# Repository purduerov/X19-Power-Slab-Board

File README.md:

# Purdue ROV KiCad Board Template

Starter template for new PCB designs in Purdue ROV. Pre-configured with the team component library submodule, automatic Git clean filters, isolation rules, and CI/CD validation.

---

## 🚀 Quickstart: Opening the Project (Recommended)

**Always open the project using the 1-click launcher:**

* **Windows:** Double-click `LAUNCH_KICAD.bat`
* **macOS / Linux:** Run `./LAUNCH_KICAD.sh`

### What the Launcher Does Automatically:
1. ⚙️ **Configures Git Hooks & Clean Filters:** Sets up Git to strip volatile viewport/zoom coordinates on every commit, preventing merge conflicts.
2. 🔄 **Auto-Updates Component Library:** Pulls the freshest symbols, footprints, and 3D models from `purdue-rov-kicad-lib` before opening.
3. 📐 **Opens KiCad:** Launches the project file with all 6 central library categories pre-linked.

---

## Creating a New Board Repository

1. In GitHub, click **Use this template** > **Create a new repository**.
2. Name the repo to match the board function (e.g. `thruster-interface-board`).
3. Clone recursively so submodules are pulled:
   ```bash
   git clone --recursive https://github.com/purduerov/<your-repo-name>.git
   cd <your-repo-name>
   ```
   If cloned without `--recursive`, initialize the submodule:
   ```bash
   git submodule update --init --recursive
   ```

4. Prepare the board with `bootstrap.py` (renames starter files, writes the manifest, and installs the validation hook; `LAUNCH_KICAD` runs this automatically):
   ```bash
   python bootstrap.py --project-dir . --non-interactive
   ```

## Central Component Library & Manager GUI

The template is pre-configured with project-level library tables (`sym-lib-table` and `fp-lib-table`) pointing to `purdue-rov-kicad-lib`:
- `rov_passives`: Resistors, capacitors, inductors, crystals
- `rov_power`: Voltage regulators, buck/boost converters, MOSFETs, diodes
- `rov_logic`: MCUs, logic ICs, op-amps, level shifters, transceivers
- `rov_connectors`: Power terminals, XT60/XT30, headers, USB, JST connectors
- `rov_sensors`: IMUs, temperature, pressure sensors
- `rov_mech`: Mounting holes, standoffs, test points

### Launching the Library Manager GUI
To browse parts, inspect footprints, edit properties, or add/delete components in the shared library:
- **Windows:** Double-click `libs\purdue-rov-kicad-lib\LIBRARY_MANAGER.bat`
- **macOS / Linux:** Run `./libs/purdue-rov-kicad-lib/LIBRARY_MANAGER.sh`

## Design Rules & Clearances

- Clearance rules are defined in `custom_rules.kicad_dru`.
- High-power thruster nets require a minimum 2.0 mm clearance from low-voltage logic (3.3V / 5V).

## Automated CI/CD & DevOps Preflight Checks

All CI/CD automation and tooling are centralized in [`purduerov/pcb-devops`](https://github.com/purduerov/pcb-devops):
1. **Automated Git Clean Filters:** Configured automatically by `.githooks/pre-commit` to prevent viewport/zoom merge noise.
2. **KiCad Symbol Linting:** Validates mandatory fields (`MPN`, `Manufacturer`, `Category`, `DigiKey`, `Datasheet`, `Temp_Range`) on all library components.
3. **ERC & DRC Validation:** Executes Electrical and Design Rules Checks via KiBot in GitHub Actions.
4. **Artifact Generation:** Automatically exports Schematic PDFs, Board Layout PDFs, and Interactive HTML BOMs on every pull request.

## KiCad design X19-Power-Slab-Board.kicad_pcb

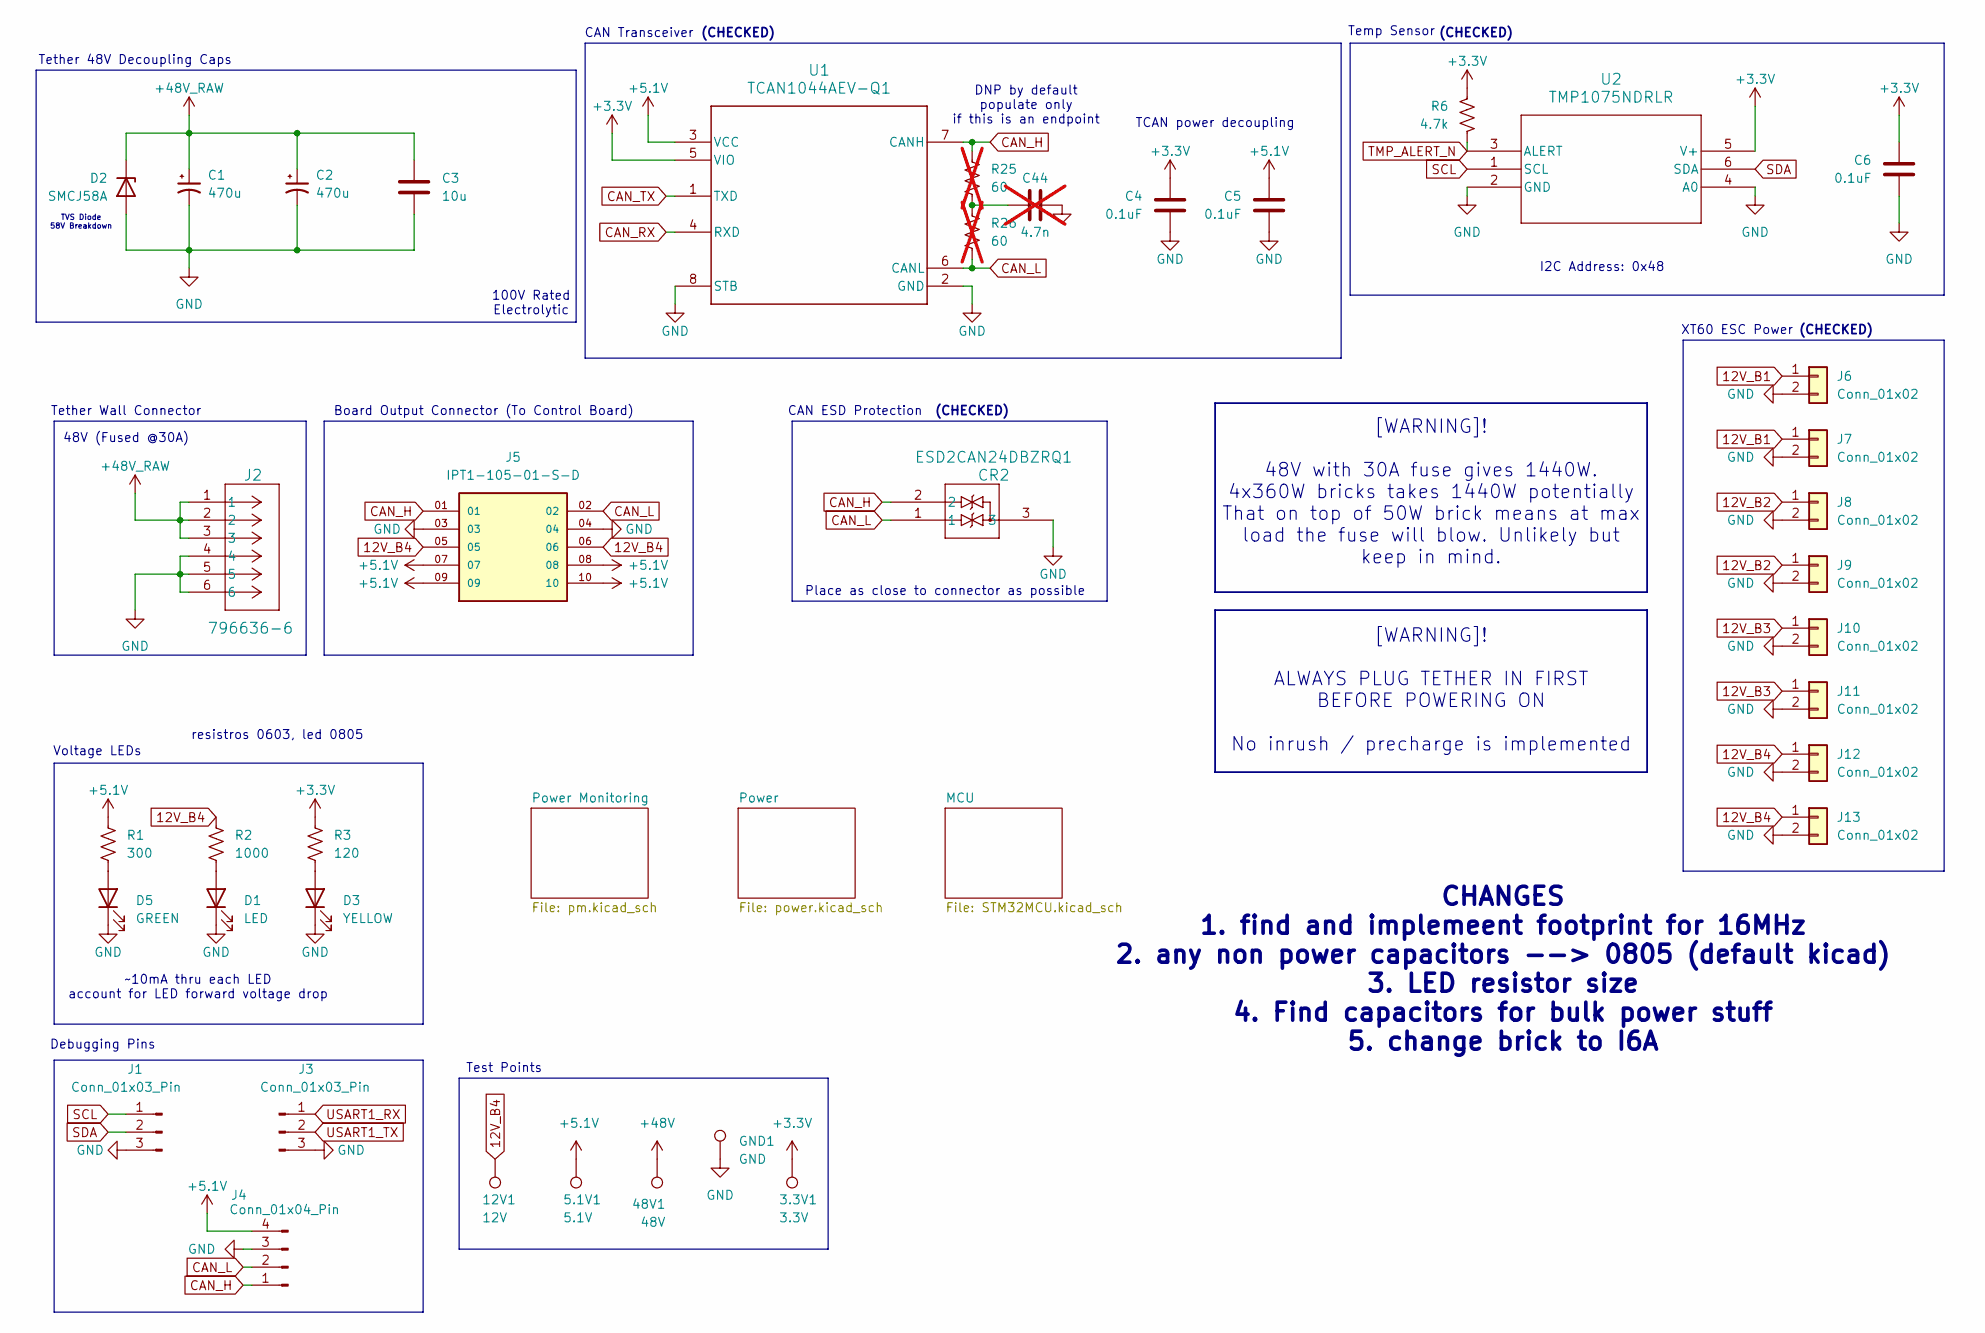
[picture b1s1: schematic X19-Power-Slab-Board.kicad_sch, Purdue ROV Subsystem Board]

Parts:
3.3V1: 3.3V; TestPoint_Pad_D2.5mm
5.1V1: 5.1V; TestPoint_Pad_D2.5mm
12V1: 12V; TestPoint_Pad_D4.0mm
48V1: 48V; TestPoint_Pad_D4.0mm
C1, C2: 470u; CP_Radial_D13.0mm_P5.00mm
C3: 10u; C_1206_3216Metric_Pad1.33x1.80mm_HandSolder
C4, C5, C6: 0.1uF; C_0603_1608Metric_Pad1.08x0.95mm_HandSolder
C44: 4.7n; C_0603_1608Metric_Pad1.08x0.95mm_HandSolder; not fitted
CR2: ESD2CAN24DBZRQ1; SOT-23_Handsoldering
D1: LED; LED_0805_2012Metric_Pad1.15x1.40mm_HandSolder
D2: SMCJ58A; D_SMC
D3: YELLOW; LED_0805_2012Metric_Pad1.15x1.40mm_HandSolder
D5: GREEN; LED_0805_2012Metric_Pad1.15x1.40mm_HandSolder
GND1: GND; TestPoint_Pad_D2.5mm
J1, J3: Conn_01x03_Pin; PinHeader_1x03_P2.54mm_Vertical
J2: 796636-6; CON6_P5MM_VER_TERM-BLK_TYC
J4: Conn_01x04_Pin; PinHeader_1x04_P2.54mm_Vertical
J5: IPT1-105-01-S-D; SAMTEC_IPT1-105-01-S-D; PARTREV R
J6, J7, J8, J9, J10, J11, J12, J13: Conn_01x02; AMASS_XT60PB-M
R1: 300; R_0603_1608Metric_Pad0.98x0.95mm_HandSolder
R2: 1000; R_0603_1608Metric_Pad0.98x0.95mm_HandSolder
R3: 120; R_0603_1608Metric_Pad0.98x0.95mm_HandSolder
R6: 4.7k; R_0603_1608Metric_Pad0.98x0.95mm_HandSolder
R25, R26: 60; R_0603_1608Metric_Pad0.98x0.95mm_HandSolder; not fitted
U1: TCAN1044AEV-Q1; D0008A-IPC_A
U2: TMP1075NDRLR; SOT5X3-6_DRL_TEX

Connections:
12V_B1: J6.1, J7.1; also elsewhere on the board
12V_B2: J8.1, J9.1; also elsewhere on the board
12V_B3: J10.1, J11.1; also elsewhere on the board
12V_B4: 12V1.1 (1_1), J5.05, J5.06, J12.1, J13.1, R2.2; also elsewhere on the board
+3.3V: 3.3V1.1 (1_1), C4.1, C6.1, R3.2, R6.1, U1.5 (VIO), U2.5 (V+); also elsewhere on the board
+5.1V: 5.1V1.1 (1_1), C5.1, J4.4, J5.07, J5.08, J5.09, J5.10, R1.2, U1.3 (VCC); also elsewhere on the board
+48V: 48V1.1 (1_1); also elsewhere on the board
+48V_RAW: C1.1, C2.1, C3.1, D2.1 (K), J2.1, J2.2, J2.3; also elsewhere on the board
CAN_H: CR2.2, J4.1, J5.01, R25.1, U1.7 (CANH)
CAN_L: CR2.1, J4.2, J5.02, R26.2, U1.6 (CANL)
CAN_RX: U1.4 (RXD); also elsewhere on the board
CAN_TX: U1.1 (TXD); also elsewhere on the board
GND: C1.2, C2.2, C3.2, C4.2, C5.2, C6.2, C44.2, CR2.3, D1.1 (K), D2.2 (A), D3.1 (K), D5.1 (K), GND1.1 (1_1), J1.3, J2.4, J2.5, J2.6, J3.3, J4.3, J5.03, J5.04, J6.2, J7.2, J8.2, J9.2, J10.2, J11.2, J12.2, J13.2, U1.2 (GND), U1.8 (STB), U2.2 (GND), U2.4 (A0); also elsewhere on the board
unnamed: C44.1, R25.2, R26.1
unnamed: D1.2 (A), R2.1
unnamed: D3.2 (A), R3.1
unnamed: D5.2 (A), R1.1
SCL: J1.1, U2.1 (SCL); also elsewhere on the board
SDA: J1.2, U2.6 (SDA); also elsewhere on the board
TMP_ALERT_N: R6.2, U2.3 (ALERT); also elsewhere on the board
USART1_RX: J3.1; also elsewhere on the board
USART1_TX: J3.2; also elsewhere on the board

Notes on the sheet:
TCAN power decoupling
(CHECKED)
resistros 0603, led 0805
100V Rated Electrolytic
XT60 ESC Power
CAN Transceiver
I2C Address: 0x48
DNP by default populate only if this is an endpoint
[WARNING]! 48V with 30A fuse gives 1440W. 4x360W bricks takes 1440W potentially That on top of 50W brick means at max load the fuse will blow. Unlikely but keep in mind.
Place as close to connector as possible
Temp Sensor
Board Output Connector (To Control Board)
TVS Diode 58V Breakdown
~10mA thru each LED account for LED forward voltage drop
CAN ESD Protection
Tether 48V Decoupling Caps
Voltage LEDs
CHANGES 1. find and implemeent footprint for 16MHz 2. any non power capacitors --> 0805 (default kicad) 3. LED resistor size 4. Find capacitors for bulk power stuff 5. change brick to I6A
[WARNING]! ALWAYS PLUG TETHER IN FIRST BEFORE POWERING ON No inrush / precharge is implemented
Test Points
Debugging Pins
Tether Wall Connector
48V (Fused @30A)

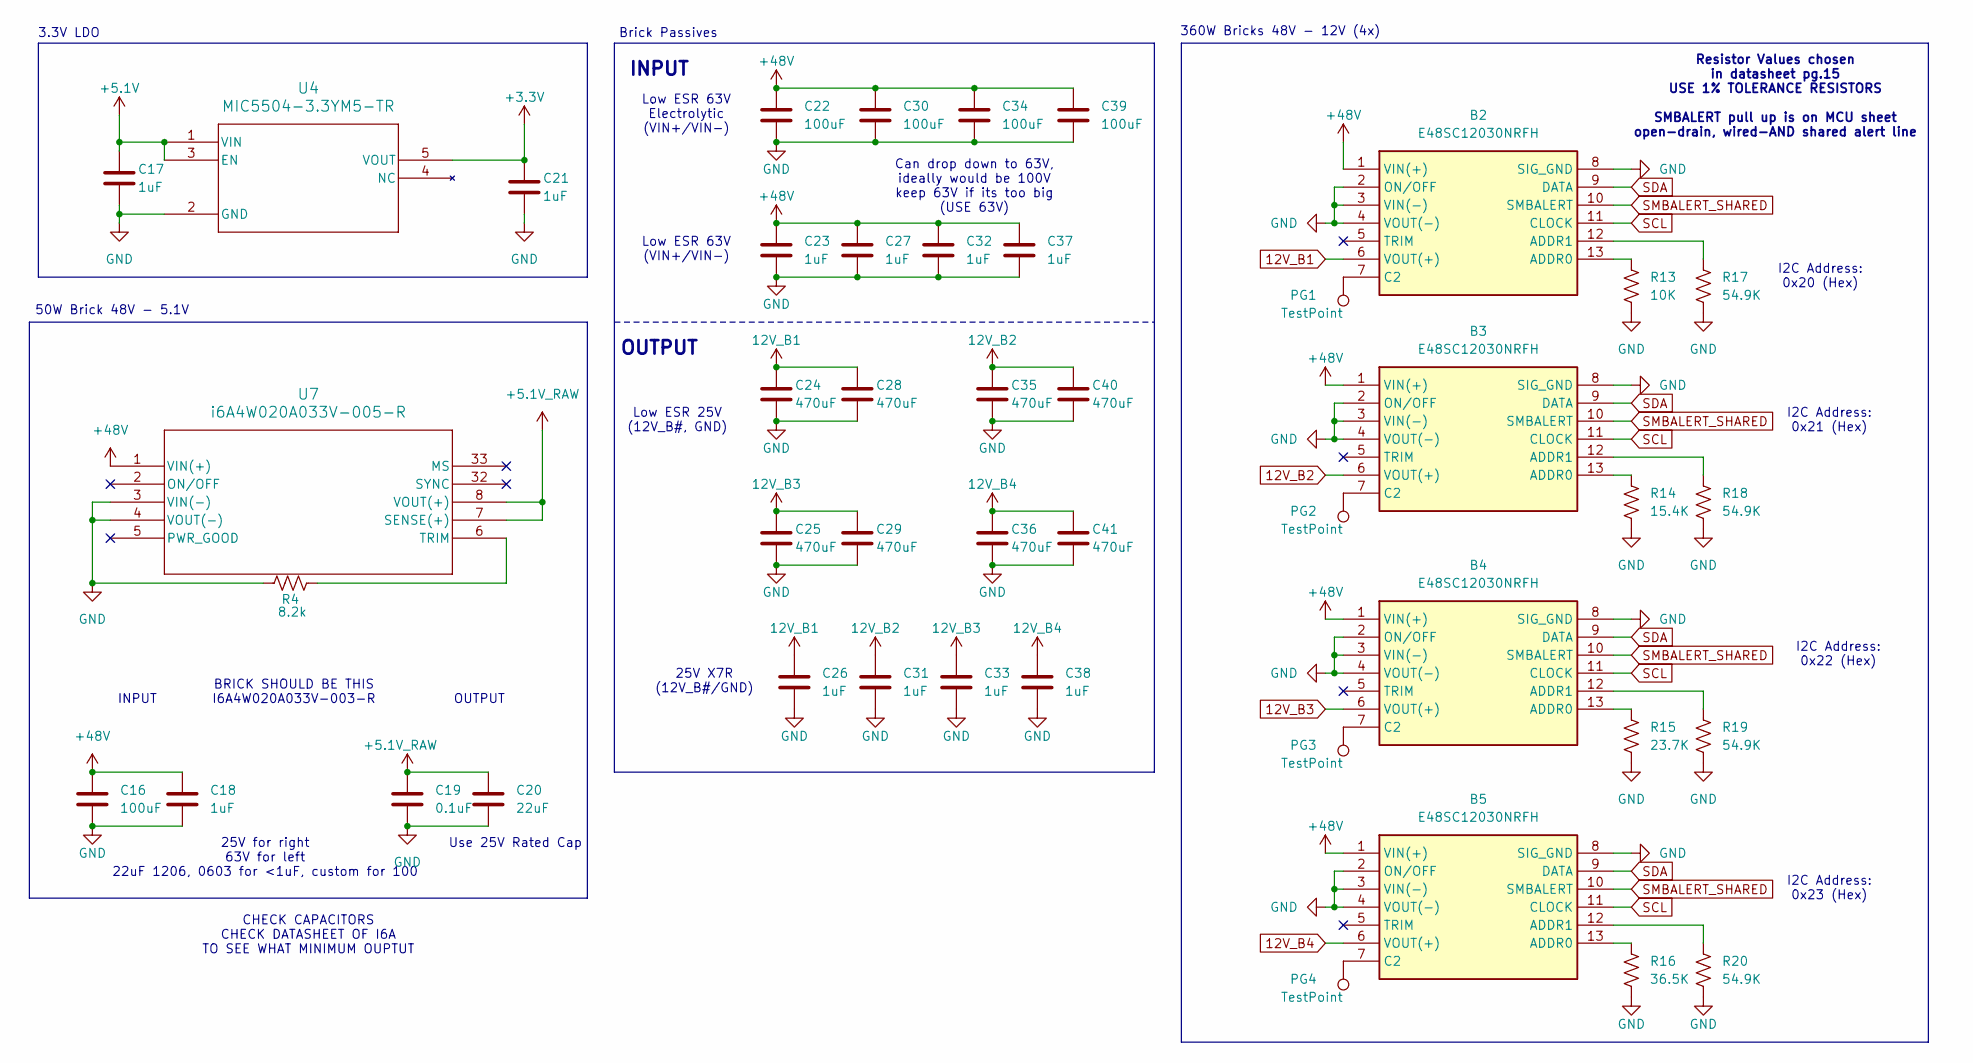
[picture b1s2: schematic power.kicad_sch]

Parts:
B2, B3, B4, B5: E48SC12030NRFH; Manufacturer_Part_Number E48SC12030NRFH
C16, C22, C30, C34, C39: 100uF; CP_Radial_D10.0mm_P5.00mm
C17, C18, C21: 1uF; C_0603_1608Metric_Pad1.08x0.95mm_HandSolder
C19: 0.1uF; C_0603_1608Metric_Pad1.08x0.95mm_HandSolder
C20: 22uF; C_1206_3216Metric_Pad1.33x1.80mm_HandSolder
C23, C26, C27, C31, C32, C33, C37, C38: 1uF; C_0805_2012Metric_Pad1.18x1.45mm_HandSolder
C24, C25, C28, C29, C35, C36, C40, C41: 470uF; CP_Radial_D10.0mm_P5.00mm
PG1, PG2, PG3, PG4: TestPoint; TestPoint_Pad_D2.5mm
R4: 8.2k; R_0603_1608Metric_Pad0.98x0.95mm_HandSolder
R13: 10K; R_0603_1608Metric_Pad0.98x0.95mm_HandSolder
R14: 15.4K; R_0603_1608Metric_Pad0.98x0.95mm_HandSolder
R15: 23.7K; R_0603_1608Metric_Pad0.98x0.95mm_HandSolder
R16: 36.5K; R_0603_1608Metric_Pad0.98x0.95mm_HandSolder
R17, R18, R19, R20: 54.9K; R_0603_1608Metric_Pad0.98x0.95mm_HandSolder
U4: MIC5504-3.3YM5-TR; SOT-23-5_MC_MCH
U7: i6A4W020A033V-005-R; i6A4W_DIP_FULL_TDK

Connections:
12V_B1: B2.6 (VOUT(+)), C24.1, C26.1, C28.1; also elsewhere on the board
12V_B2: B3.6 (VOUT(+)), C31.1, C35.1, C40.1; also elsewhere on the board
12V_B3: B4.6 (VOUT(+)), C25.1, C29.1, C33.1; also elsewhere on the board
12V_B4: B5.6 (VOUT(+)), C36.1, C38.1, C41.1; also elsewhere on the board
+3.3V: C21.1, U4.5 (VOUT); also elsewhere on the board
+5.1V: C17.1, U4.1 (VIN), U4.3 (EN); also elsewhere on the board
+5.1V_RAW: C19.1, C20.1, U7.7 (SENSE(+)), U7.8 (VOUT(+)); also elsewhere on the board
+48V: B2.1 (VIN(+)), B3.1 (VIN(+)), B4.1 (VIN(+)), B5.1 (VIN(+)), C16.1, C18.1, C22.1, C23.1, C27.1, C30.1, C32.1, C34.1, C37.1, C39.1, U7.1 (VIN(+)); also elsewhere on the board
GND: B2.2 (ON/OFF), B2.3 (VIN(-)), B2.4 (VOUT(-)), B2.8 (SIG_GND), B3.2 (ON/OFF), B3.3 (VIN(-)), B3.4 (VOUT(-)), B3.8 (SIG_GND), B4.2 (ON/OFF), B4.3 (VIN(-)), B4.4 (VOUT(-)), B4.8 (SIG_GND), B5.2 (ON/OFF), B5.3 (VIN(-)), B5.4 (VOUT(-)), B5.8 (SIG_GND), C16.2, C17.2, C18.2, C19.2, C20.2, C21.2, C22.2, C23.2, C24.2, C25.2, C26.2, C27.2, C28.2, C29.2, C30.2, C31.2, C32.2, C33.2, C34.2, C35.2, C36.2, C37.2, C38.2, C39.2, C40.2, C41.2, R4.1, R13.2, R14.2, R15.2, R16.2, R17.2, R18.2, R19.2, R20.2, U4.2 (GND), U7.3 (VIN(-)), U7.4 (VOUT(-)); also elsewhere on the board
unnamed: B2.13 (ADDR0), R13.1
unnamed: B2.12 (ADDR1), R17.1
unnamed: B2.7 (C2), PG1.1 (1_1)
unnamed: B3.13 (ADDR0), R14.1
unnamed: B3.12 (ADDR1), R18.1
unnamed: B3.7 (C2), PG2.1 (1_1)
unnamed: B4.13 (ADDR0), R15.1
unnamed: B4.12 (ADDR1), R19.1
unnamed: B4.7 (C2), PG3.1 (1_1)
unnamed: B5.13 (ADDR0), R16.1
unnamed: B5.12 (ADDR1), R20.1
unnamed: B5.7 (C2), PG4.1 (1_1)
unnamed: R4.2, U7.6 (TRIM)
SCL: B2.11 (CLOCK), B3.11 (CLOCK), B4.11 (CLOCK), B5.11 (CLOCK); also elsewhere on the board
SDA: B2.9 (DATA), B3.9 (DATA), B4.9 (DATA), B5.9 (DATA); also elsewhere on the board
SMBALERT_SHARED: B2.10 (SMBALERT), B3.10 (SMBALERT), B4.10 (SMBALERT), B5.10 (SMBALERT); also elsewhere on the board

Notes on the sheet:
3.3V LDO
CHECK CAPACITORS CHECK DATASHEET OF I6A TO SEE WHAT MINIMUM OUPTUT
360W Bricks 48V - 12V (4x)
Brick Passives
Low ESR 63V (VIN+/VIN-)
50W Brick 48V - 5.1V
Use 25V Rated Cap
OUTPUT
INPUT
I2C Address: 0x21 (Hex)
Low ESR 63V Electrolytic (VIN+/VIN-)
I2C Address: 0x20 (Hex)
Low ESR 25V (12V_B#, GND)
25V for right 63V for left 22uF 1206, 0603 for <1uF, custom for 100
BRICK SHOULD BE THIS I6A4W020A033V-003-R
Resistor Values chosen in datasheet pg.15 USE 1% TOLERANCE RESISTORS SMBALERT pull up is on MCU sheet open-drain, wired-AND shared alert line
25V X7R (12V_B#/GND)
I2C Address: 0x22 (Hex)
Can drop down to 63V, ideally would be 100V keep 63V if its too big (USE 63V)
I2C Address: 0x23 (Hex)

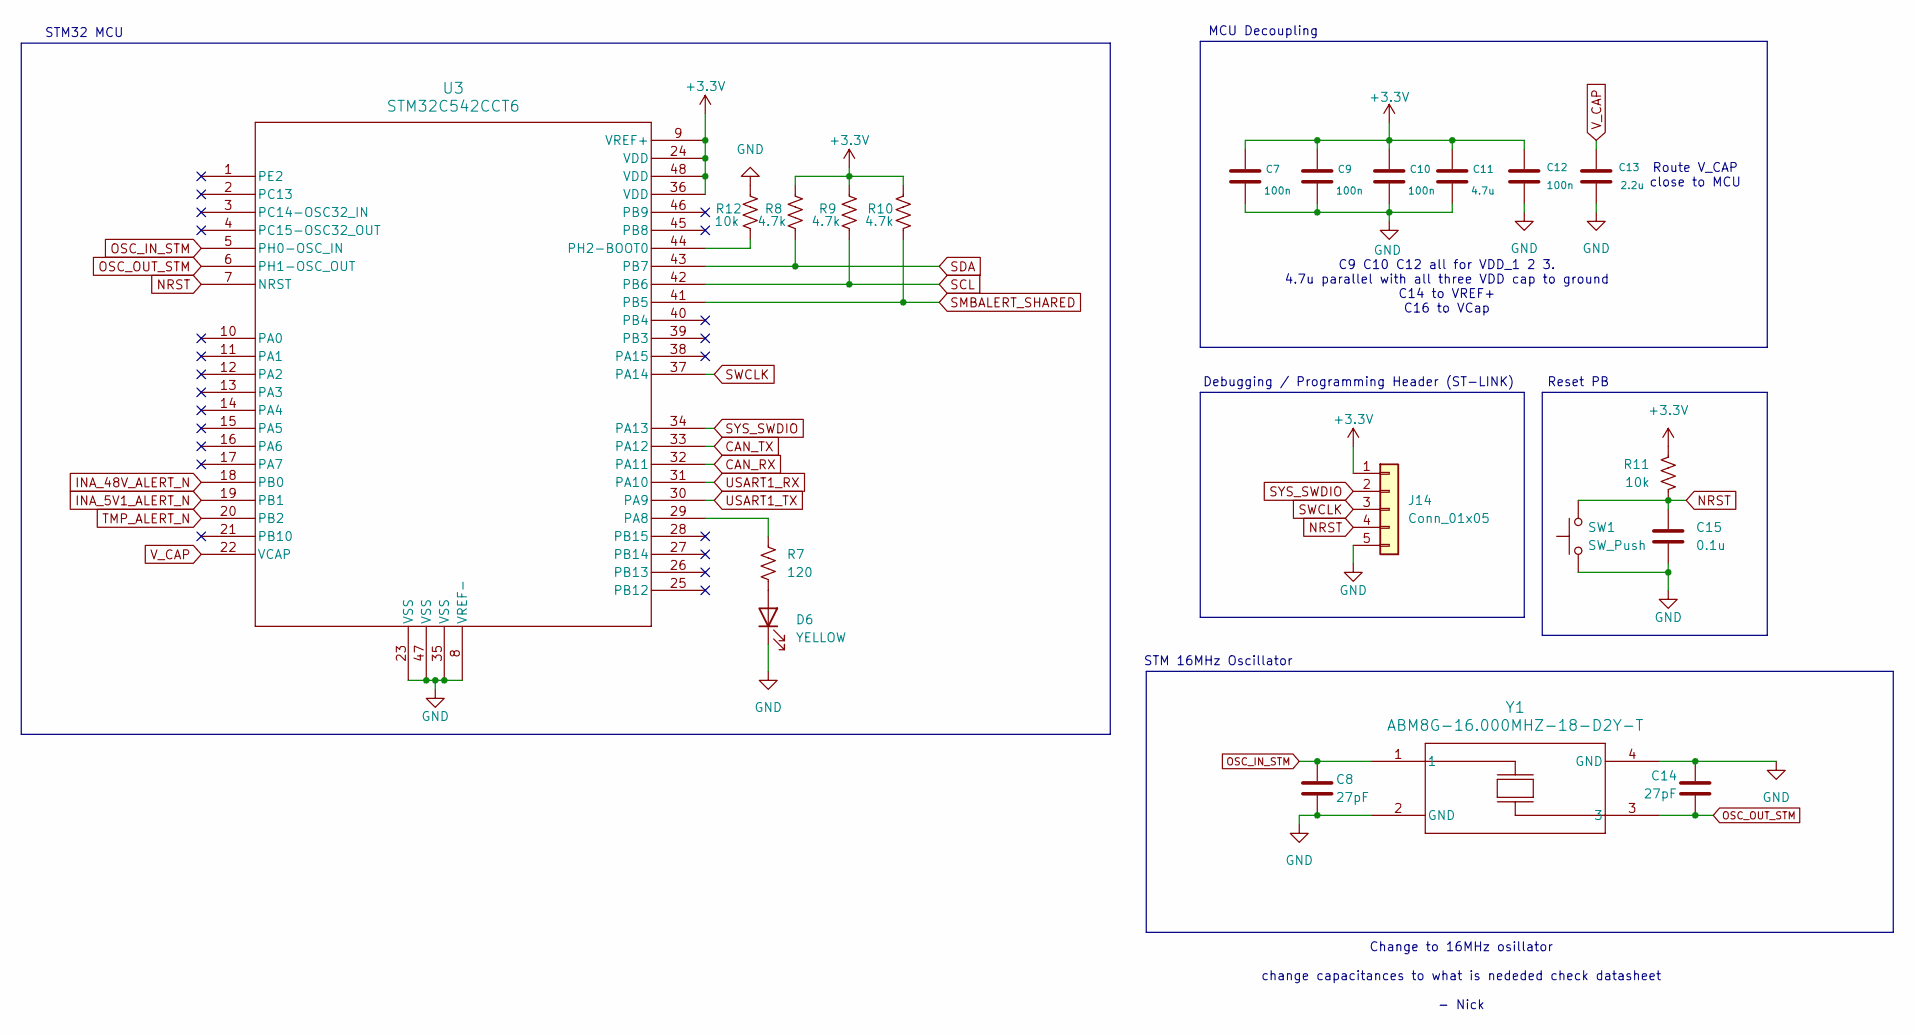
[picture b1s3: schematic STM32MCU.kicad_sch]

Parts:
C7, C9, C10, C12: 100n; C_0603_1608Metric_Pad1.08x0.95mm_HandSolder
C8, C14: 27pF; C_0603_1608Metric_Pad1.08x0.95mm_HandSolder
C11: 4.7u; C_0603_1608Metric_Pad1.08x0.95mm_HandSolder
C13: 2.2u; C_0603_1608Metric_Pad1.08x0.95mm_HandSolder
C15: 0.1u; C_0603_1608Metric_Pad1.08x0.95mm_HandSolder
D6: YELLOW; LED_0805_2012Metric_Pad1.15x1.40mm_HandSolder
J14: Conn_01x05; PinHeader_1x05_P2.54mm_Vertical
R7: 120; R_0603_1608Metric_Pad0.98x0.95mm_HandSolder
R8, R9, R10: 4.7k; R_0603_1608Metric_Pad0.98x0.95mm_HandSolder
R11, R12: 10k; R_0603_1608Metric_Pad0.98x0.95mm_HandSolder
SW1: SW_Push; SW_SPST_B3U-1000P
U3: STM32C542CCT6; LQFP48-7X7
Y1: ABM8G-16.000MHZ-18-D2Y-T; Crystal_SMD_3225-4Pin_3.2x2.5mm

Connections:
+3.3V: C7.1, C9.1, C10.1, C11.1, C12.1, J14.1, R8.2, R9.2, R10.1, R11.1, U3.9 (VREF+), U3.24 (VDD), U3.36 (VDD), U3.48 (VDD); also elsewhere on the board
CAN_RX: U3.32 (PA11); also elsewhere on the board
CAN_TX: U3.33 (PA12); also elsewhere on the board
GND: C7.2, C8.1, C9.2, C10.2, C11.2, C12.2, C13.2, C14.1, C15.2, D6.1 (K), J14.5, R12.2, SW1.1, U3.8 (VREF-), U3.23 (VSS), U3.35 (VSS), U3.47 (VSS), Y1.2 (GND), Y1.4 (GND); also elsewhere on the board
INA_5V1_ALERT_N: U3.19 (PB1); also elsewhere on the board
INA_48V_ALERT_N: U3.18 (PB0); also elsewhere on the board
NRST: C15.1, J14.4, R11.2, SW1.2, U3.7 (NRST)
unnamed: D6.2 (A), R7.2
unnamed: R7.1, U3.29 (PA8)
unnamed: R12.1, U3.44 (PH2-BOOT0)
OSC_IN_STM: C8.2, U3.5 (PH0-OSC_IN), Y1.1
OSC_OUT_STM: C14.2, U3.6 (PH1-OSC_OUT), Y1.3
SCL: R9.1, U3.42 (PB6); also elsewhere on the board
SDA: R8.1, U3.43 (PB7); also elsewhere on the board
SMBALERT_SHARED: R10.2, U3.41 (PB5); also elsewhere on the board
SWCLK: J14.3, U3.37 (PA14)
SYS_SWDIO: J14.2, U3.34 (PA13)
TMP_ALERT_N: U3.20 (PB2); also elsewhere on the board
USART1_RX: U3.31 (PA10); also elsewhere on the board
USART1_TX: U3.30 (PA9); also elsewhere on the board
V_CAP: C13.1, U3.22 (VCAP)

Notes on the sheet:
C9 C10 C12 all for VDD_1 2 3. 4.7u parallel with all three VDD cap to ground C14 to VREF+ C16 to VCap
Reset PB
Change to 16MHz osillator change capacitances to what is nededed check datasheet - Nick
Debugging / Programming Header (ST-LINK)
STM32 MCU
STM 16MHz Oscillator
MCU Decoupling
Route V_CAP close to MCU

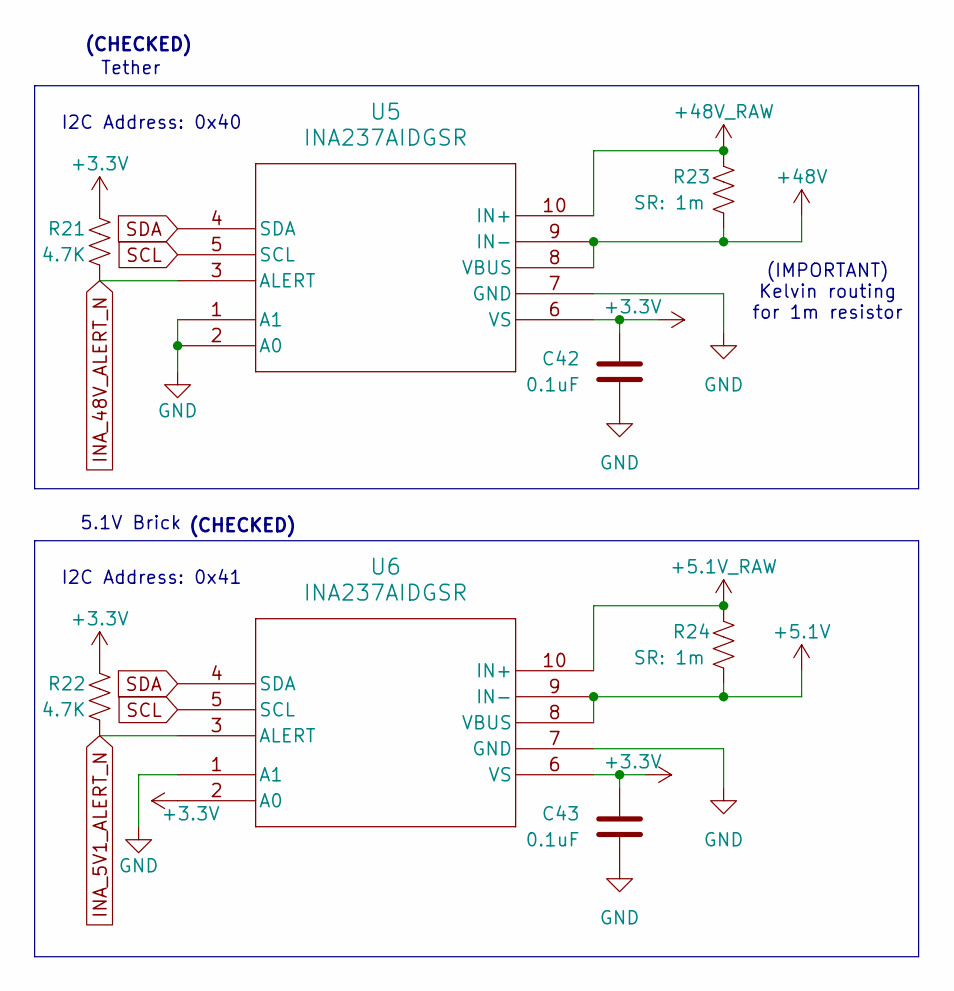
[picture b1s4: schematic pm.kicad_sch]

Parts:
C42, C43: 0.1uF; C_0603_1608Metric_Pad1.08x0.95mm_HandSolder
R21, R22: 4.7K; R_0603_1608Metric_Pad0.98x0.95mm_HandSolder
R23, R24: SR: 1m; R_2512_6332Metric_Pad1.40x3.35mm_HandSolder
U5, U6: INA237AIDGSR; VSSOP_IDGSR_TEX

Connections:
+3.3V: C42.1, C43.1, R21.1, R22.1, U5.6 (VS), U6.2 (A0), U6.6 (VS); also elsewhere on the board
+5.1V: R24.2, U6.8 (VBUS), U6.9 (IN-); also elsewhere on the board
+5.1V_RAW: R24.1, U6.10 (IN+); also elsewhere on the board
+48V: R23.2, U5.8 (VBUS), U5.9 (IN-); also elsewhere on the board
+48V_RAW: R23.1, U5.10 (IN+); also elsewhere on the board
GND: C42.2, C43.2, U5.1 (A1), U5.2 (A0), U5.7 (GND), U6.1 (A1), U6.7 (GND); also elsewhere on the board
INA_5V1_ALERT_N: R22.2, U6.3 (ALERT); also elsewhere on the board
INA_48V_ALERT_N: R21.2, U5.3 (ALERT); also elsewhere on the board
SCL: U5.5 (SCL), U6.5 (SCL); also elsewhere on the board
SDA: U5.4 (SDA), U6.4 (SDA); also elsewhere on the board

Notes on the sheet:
Tether
(IMPORTANT) Kelvin routing for 1m resistor
(CHECKED)
5.1V Brick
I2C Address: 0x41
I2C Address: 0x40

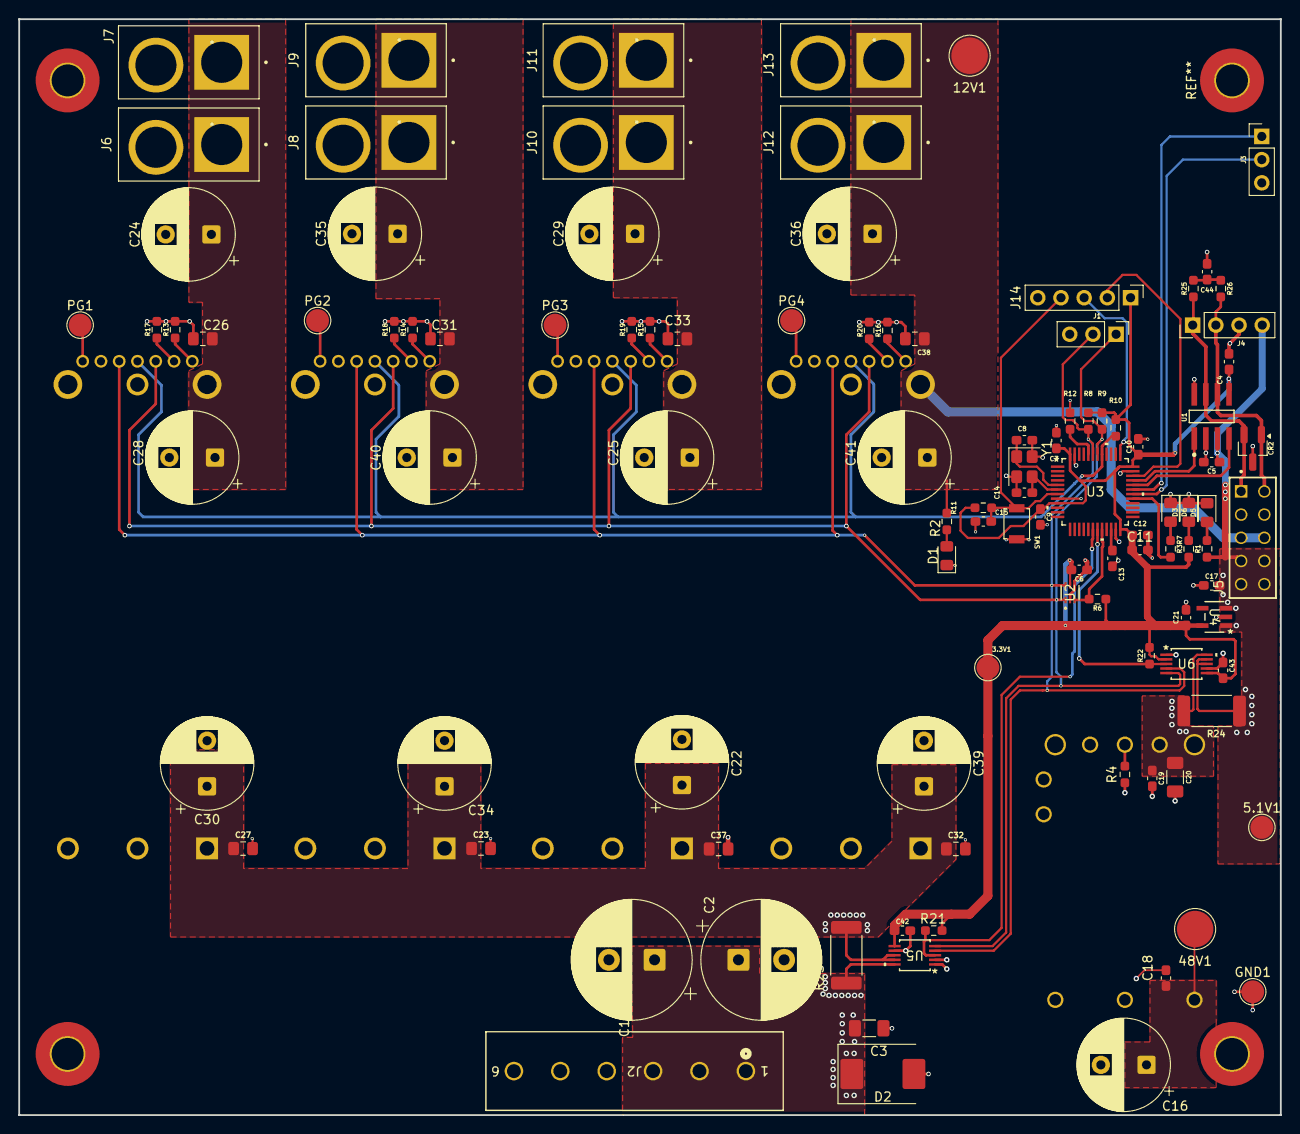
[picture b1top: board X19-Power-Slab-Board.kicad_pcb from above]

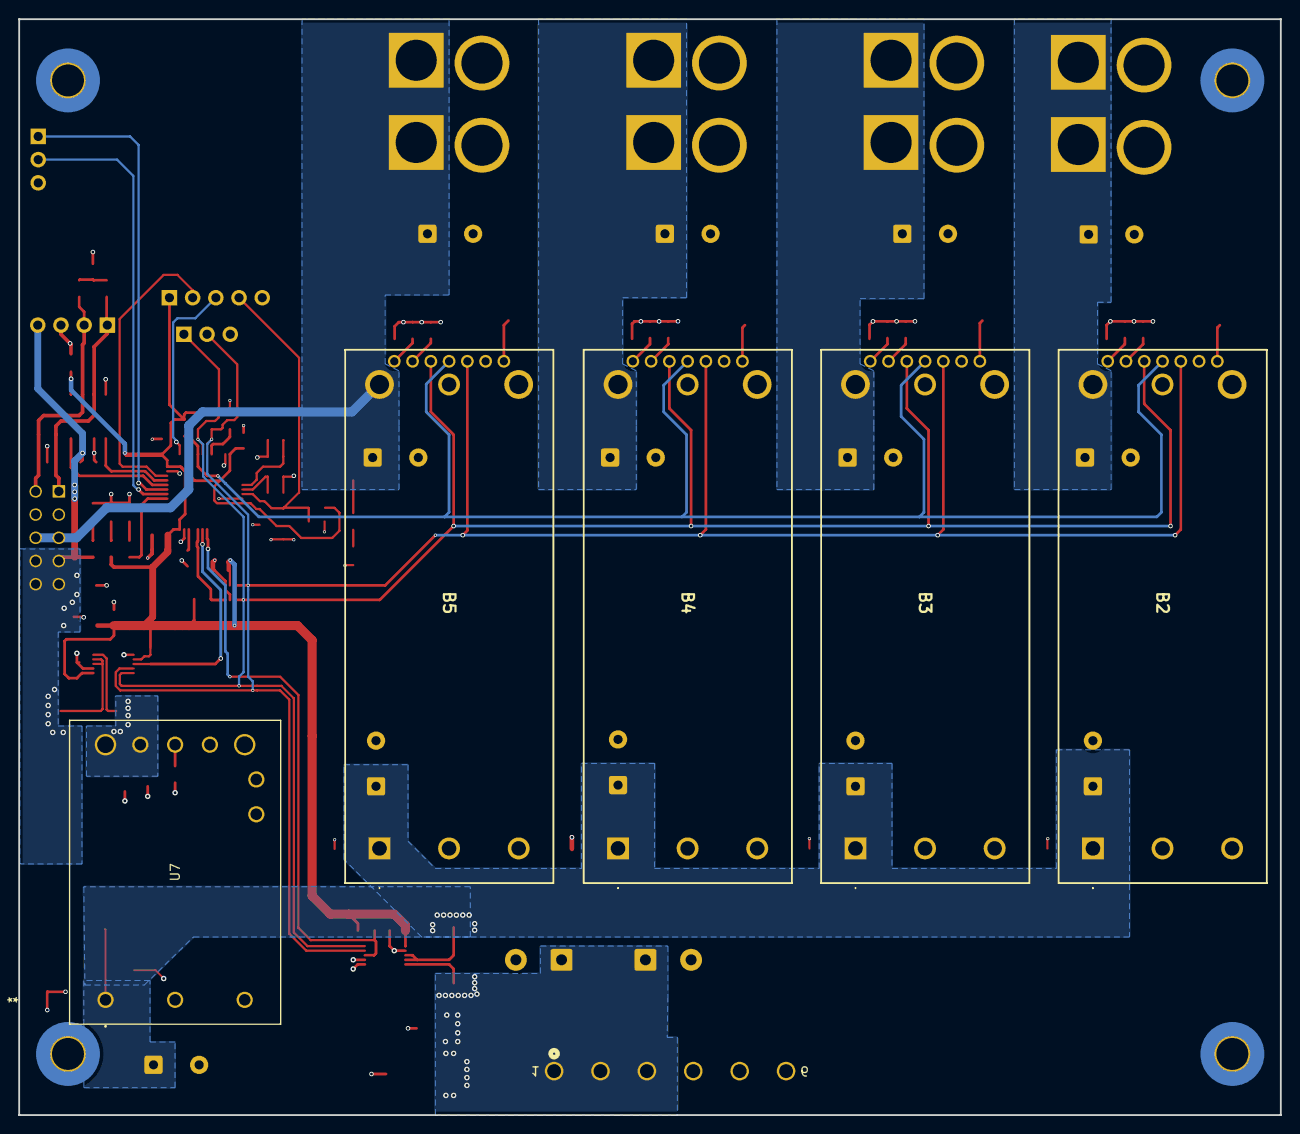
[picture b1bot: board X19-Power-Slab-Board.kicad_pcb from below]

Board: 4 copper layers, 138.1 x 120.0 mm, 111 parts (5 on the bottom side), 48 nets.
